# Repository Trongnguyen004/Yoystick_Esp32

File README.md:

# Yoystick_Esp32
### #Mô hình làm chơi lấy kinh nghiệm làm mạch nên không được ứng dụng vào thực tế 😅 
### 3D PCB

### Tham khảo

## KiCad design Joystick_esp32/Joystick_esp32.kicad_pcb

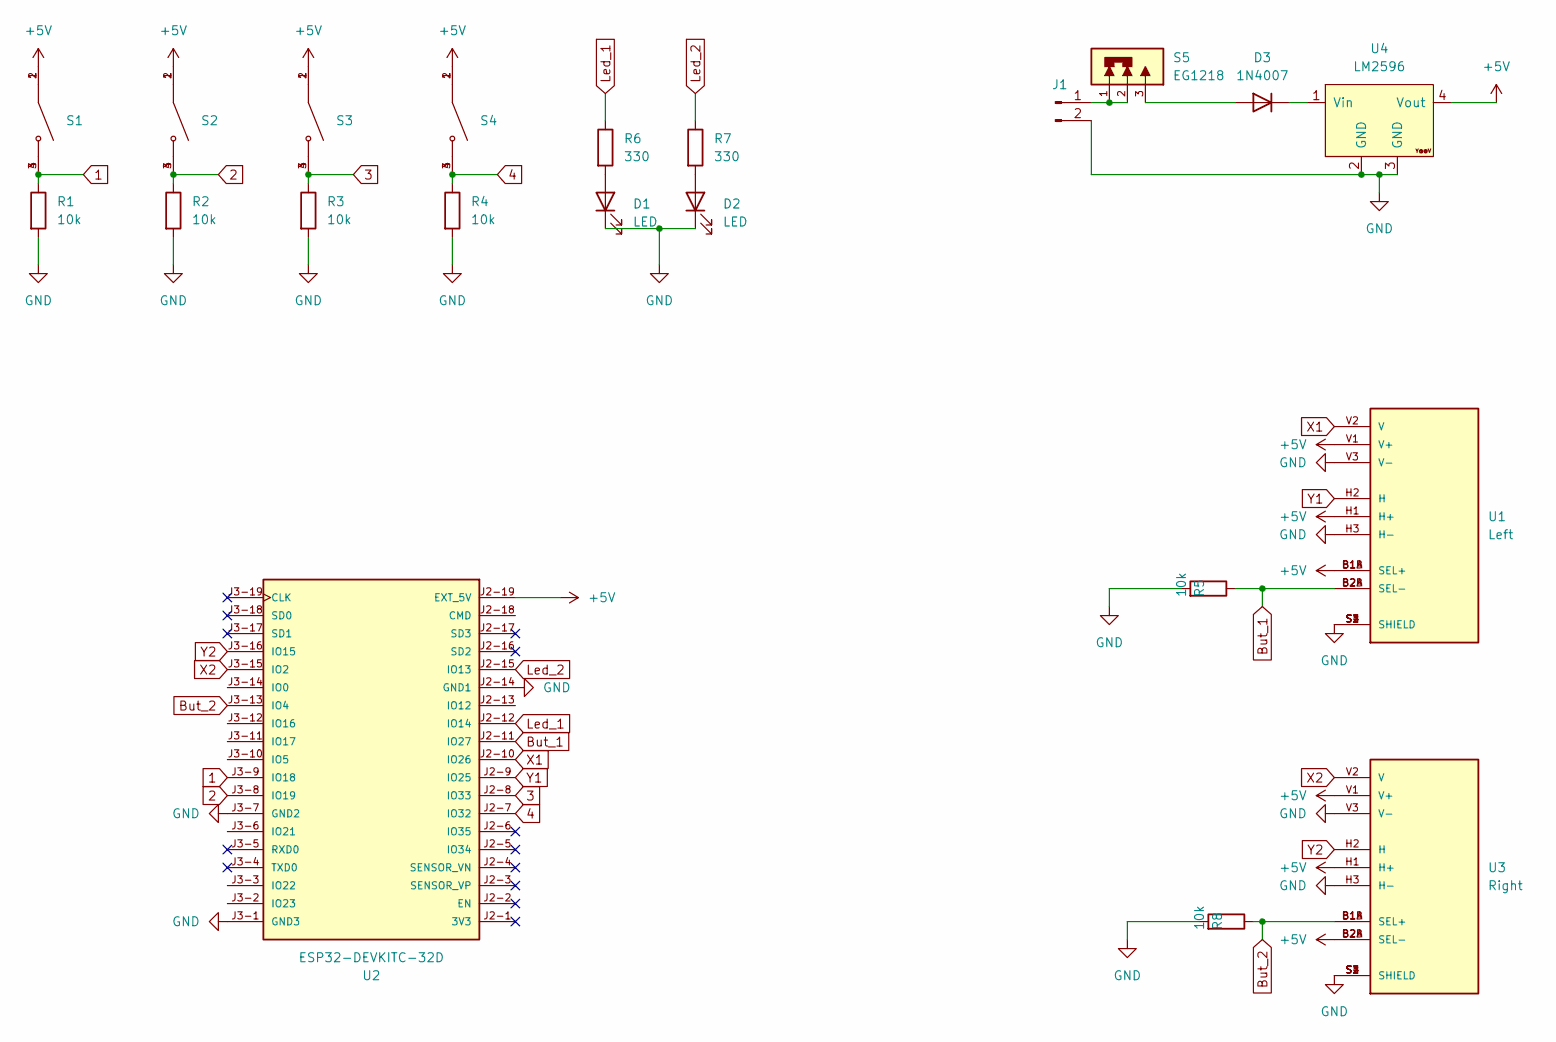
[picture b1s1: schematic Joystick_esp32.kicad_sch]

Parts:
D1, D2: LED; LED_D5.0mm
D3: 1N4007; D_DO-41_SOD81_P7.62mm_Horizontal
J1: PinSocket_1x02_P2.54mm_Vertical
R1, R2, R3, R4, R5, R8: 10k; R_Axial_DIN0207_L6.3mm_D2.5mm_P7.62mm_Horizontal
R6, R7: 330; R_Axial_DIN0207_L6.3mm_D2.5mm_P7.62mm_Horizontal
S1, S2, S3, S4: SW_B3F-4055; PARTREV A070-E1-08
S5: EG1218; SS12D00
U1: Left; XDCR_COM-09032; PARTREV N/A
U2: ESP32-DEVKITC-32D; MODULE_ESP32-DEVKITC-32D; PARTREV V4
U3: Right; XDCR_COM-09032; PARTREV N/A
U4: LM2596; YAAJ_DCDC_StepDown_LM2596

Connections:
1: R1.1, S1.3, S1.4, U2.J3-9 (IO18)
2: R2.1, S2.3, S2.4, U2.J3-8 (IO19)
3: R3.1, S3.3, S3.4, U2.J2-8 (IO33)
4: R4.1, S4.3, S4.4, U2.J2-7 (IO32)
+5V: S1.1, S1.2, S2.1, S2.2, S3.1, S3.2, S4.1, S4.2, U1.B1A (SEL+), U1.B1B (SEL+), U1.H1 (H+), U1.V1 (V+), U2.J2-19 (EXT_5V), U3.B2A (SEL-), U3.B2B (SEL-), U3.H1 (H+), U3.V1 (V+), U4.4 (Vout)
But_1: R5.1, U1.B2A (SEL-), U1.B2B (SEL-), U2.J2-11 (IO27)
But_2: R8.1, U2.J3-13 (IO4), U3.B1A (SEL+), U3.B1B (SEL+)
GND: D1.1 (K), D2.1 (K), J1.2, R1.2, R2.2, R3.2, R4.2, R5.2, R8.2, U1.H3 (H-), U1.S1 (SHIELD), U1.S2 (SHIELD), U1.S3 (SHIELD), U1.S4 (SHIELD), U1.V3 (V-), U2.J2-14 (GND1), U2.J3-1 (GND3), U2.J3-7 (GND2), U3.H3 (H-), U3.S1 (SHIELD), U3.S2 (SHIELD), U3.S3 (SHIELD), U3.S4 (SHIELD), U3.V3 (V-), U4.2 (GND), U4.3 (GND)
Led_1: R6.1, U2.J2-12 (IO14)
Led_2: R7.1, U2.J2-15 (IO13)
unnamed: D1.2 (A), R6.2
unnamed: D2.2 (A), R7.2
unnamed: D3.2 (A), S5.3
unnamed: D3.1 (K), U4.1 (Vin)
unnamed: J1.1, S5.1, S5.2
X1: U1.V2 (V), U2.J2-10 (IO26)
X2: U2.J3-15 (IO2), U3.V2 (V)
Y1: U1.H2 (H), U2.J2-9 (IO25)
Y2: U2.J3-16 (IO15), U3.H2 (H)

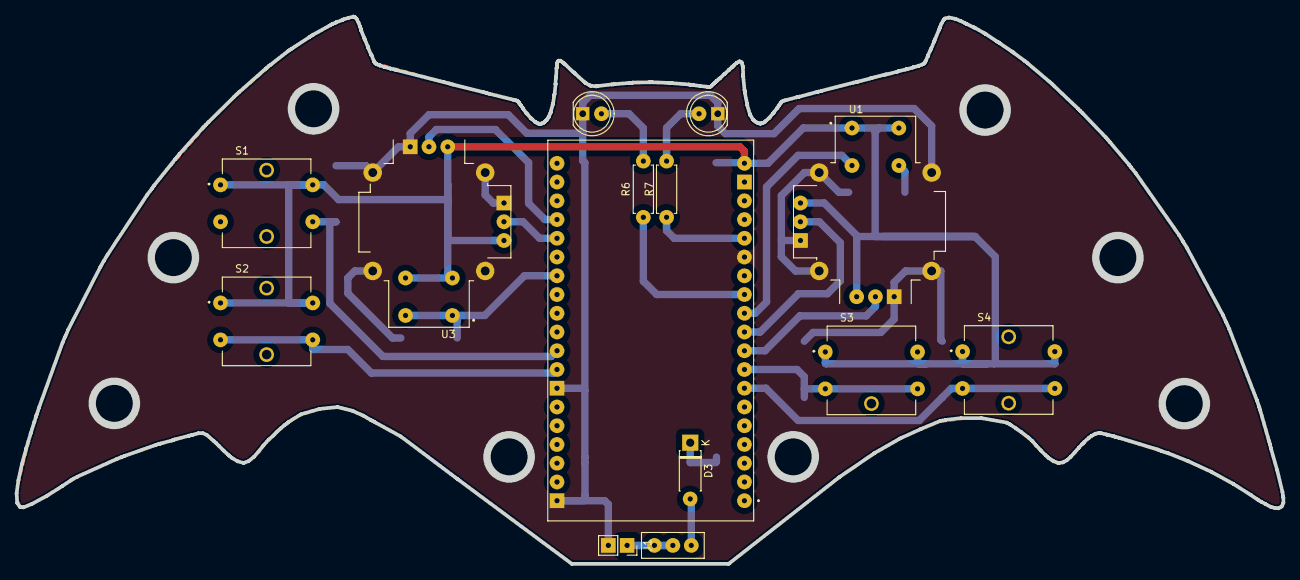
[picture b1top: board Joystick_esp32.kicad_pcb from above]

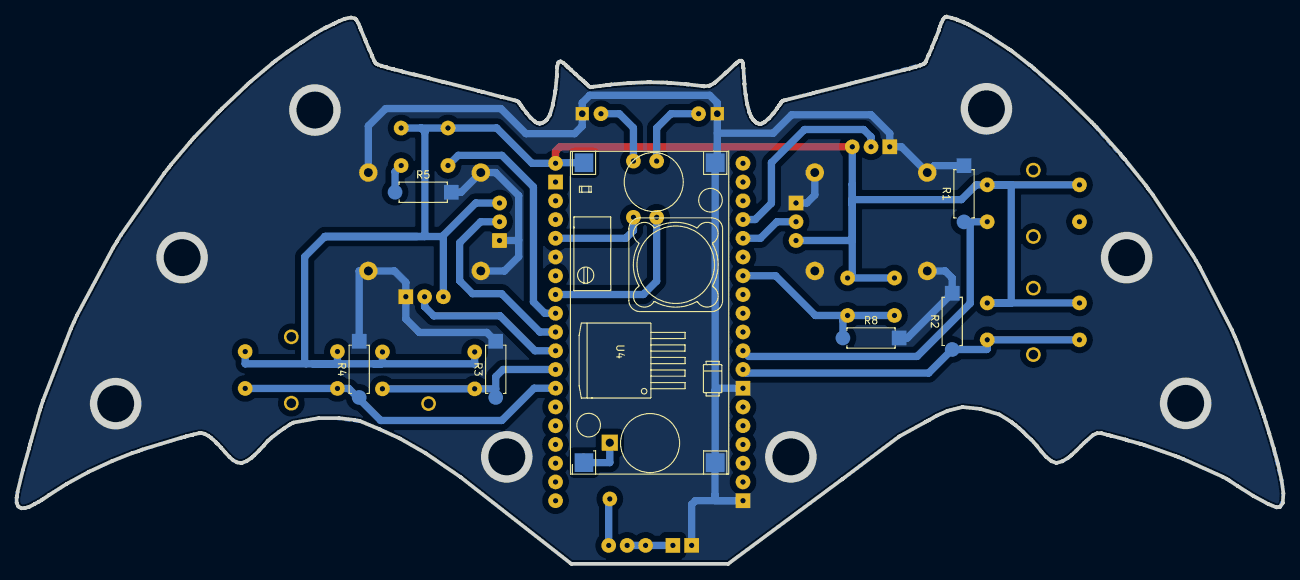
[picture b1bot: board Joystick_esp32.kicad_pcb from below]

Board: 2 copper layers, 171.7 x 74.2 mm, 21 parts (7 on the bottom side), 19 nets.
